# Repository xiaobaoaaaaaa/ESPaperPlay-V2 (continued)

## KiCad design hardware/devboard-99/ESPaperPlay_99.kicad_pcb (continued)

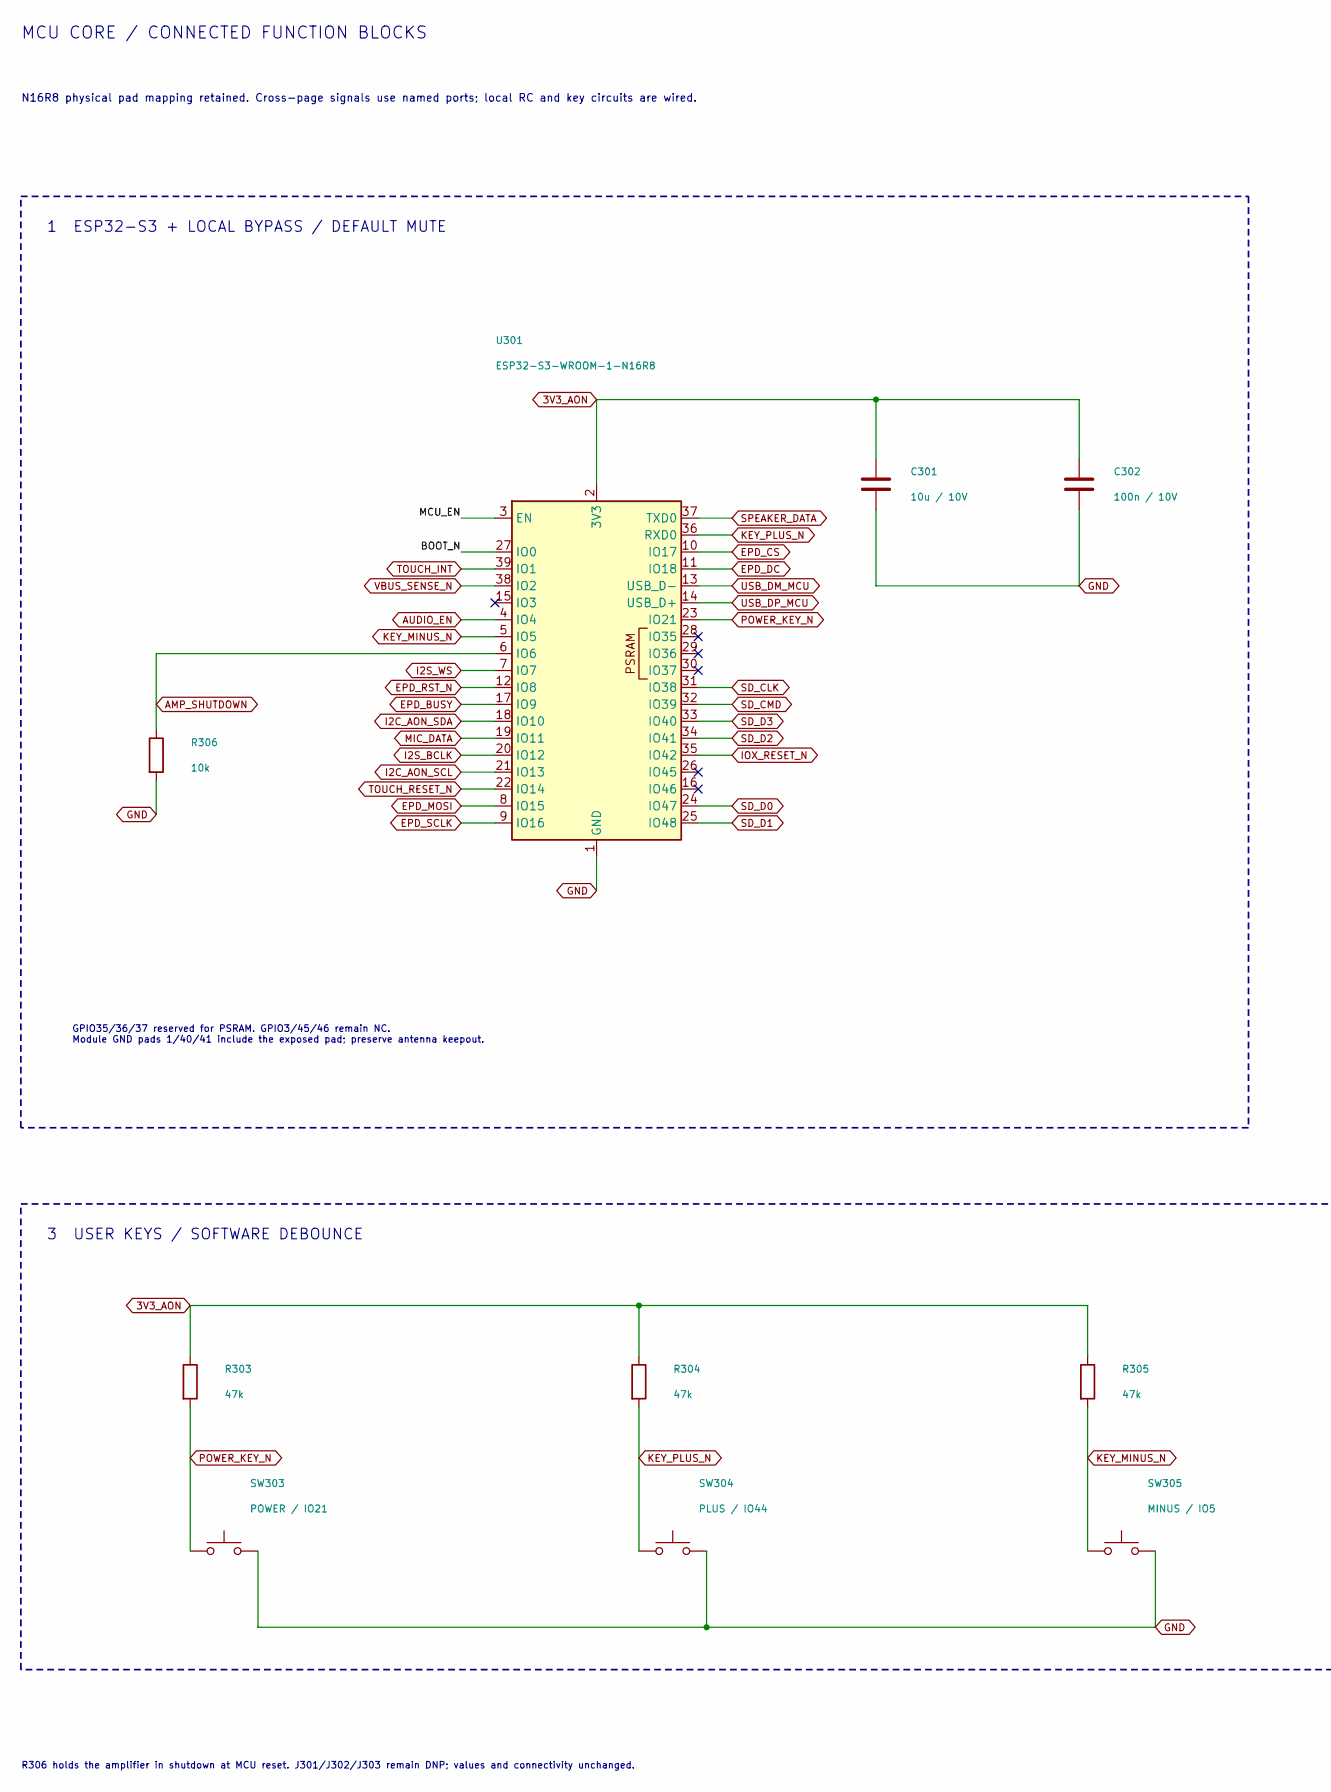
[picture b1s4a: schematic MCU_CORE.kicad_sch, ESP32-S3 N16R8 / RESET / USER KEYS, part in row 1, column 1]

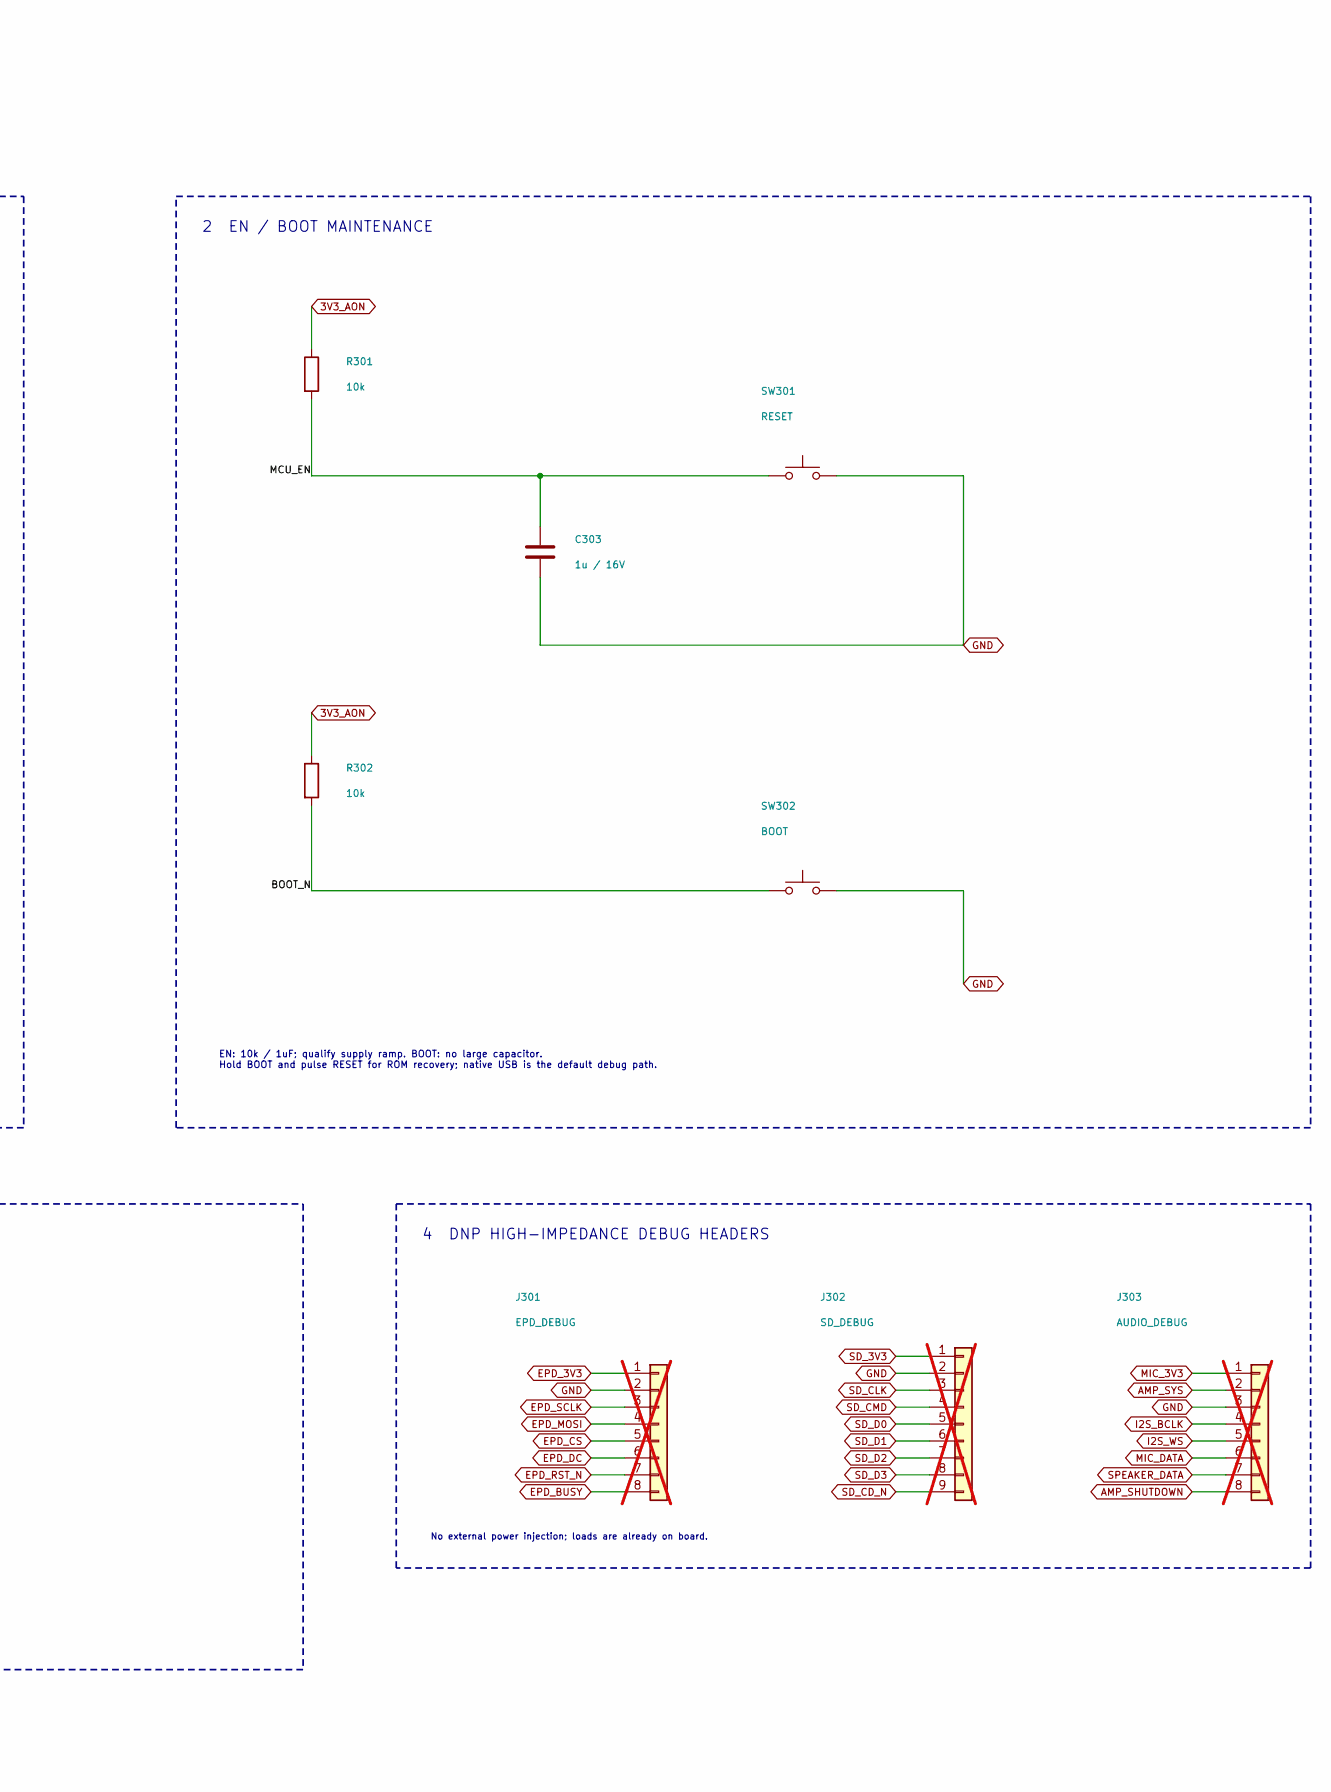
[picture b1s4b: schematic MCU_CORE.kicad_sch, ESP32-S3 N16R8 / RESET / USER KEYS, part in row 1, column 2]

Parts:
C301: 10u / 10V; C_0805_2012Metric
C302: 100n / 10V; C_0603_1608Metric
C303: 1u / 16V; C_0603_1608Metric
J301: EPD_DEBUG; WR_PHD_1x08_P2.54_Drill1.10; not fitted
J302: SD_DEBUG; WR_PHD_1x09_P2.54_Drill1.10; not fitted
J303: AUDIO_DEBUG; WR_PHD_1x08_P2.54_Drill1.10; not fitted
R301, R302, R306: 10k; R_0603_1608Metric
R303, R304, R305: 47k; R_0603_1608Metric
SW301: RESET; SW_PUSH_6mm
SW302: BOOT; SW_PUSH_6mm
SW303: POWER / IO21; SW_PUSH_6mm
SW304: PLUS / IO44; SW_PUSH_6mm
SW305: MINUS / IO5; SW_PUSH_6mm
U301: ESP32-S3-WROOM-1-N16R8; ESP32-S3-WROOM-1_030mm_PTH

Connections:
3V3_AON: C301.1, C302.1, R301.1, R302.1, R303.1, R304.1, R305.1, U301.2 (3V3); also elsewhere on the board
/MCU_CORE/BOOT_N: R302.2, SW302.1, U301.27 (IO0)
/MCU_CORE/MCU_EN: C303.1, R301.2, SW301.1, U301.3 (EN)
AMP_SHUTDOWN: J303.8, R306.1, U301.6 (IO6); also elsewhere on the board
AMP_SYS: J303.2; also elsewhere on the board
AUDIO_EN: U301.4 (IO4); also elsewhere on the board
EPD_3V3: J301.1; also elsewhere on the board
EPD_BUSY: J301.8, U301.17 (IO9); also elsewhere on the board
EPD_CS: J301.5, U301.10 (IO17); also elsewhere on the board
EPD_DC: J301.6, U301.11 (IO18); also elsewhere on the board
EPD_MOSI: J301.4, U301.8 (IO15); also elsewhere on the board
EPD_RST_N: J301.7, U301.12 (IO8); also elsewhere on the board
EPD_SCLK: J301.3, U301.9 (IO16); also elsewhere on the board
GND: C301.2, C302.2, C303.2, J301.2, J302.2, J303.3, R306.2, SW301.2, SW302.2, SW303.2, SW304.2, SW305.2, U301.1 (GND), U301.40 (GND), U301.41 (GND); also elsewhere on the board
I2C_AON_SCL: U301.21 (IO13); also elsewhere on the board
I2C_AON_SDA: U301.18 (IO10); also elsewhere on the board
I2S_BCLK: J303.4, U301.20 (IO12); also elsewhere on the board
I2S_WS: J303.5, U301.7 (IO7); also elsewhere on the board
IOX_RESET_N: U301.35 (IO42); also elsewhere on the board
KEY_MINUS_N: R305.2, SW305.1, U301.5 (IO5)
KEY_PLUS_N: R304.2, SW304.1, U301.36 (RXD0)
MIC_3V3: J303.1; also elsewhere on the board
MIC_DATA: J303.6, U301.19 (IO11); also elsewhere on the board
POWER_KEY_N: R303.2, SW303.1, U301.23 (IO21)
SD_3V3: J302.1; also elsewhere on the board
SD_CD_N: J302.9; also elsewhere on the board
SD_CLK: J302.3, U301.31 (IO38); also elsewhere on the board
SD_CMD: J302.4, U301.32 (IO39); also elsewhere on the board
SD_D0: J302.5, U301.24 (IO47); also elsewhere on the board
SD_D1: J302.6, U301.25 (IO48); also elsewhere on the board
SD_D2: J302.7, U301.34 (IO41); also elsewhere on the board
SD_D3: J302.8, U301.33 (IO40); also elsewhere on the board
SPEAKER_DATA: J303.7, U301.37 (TXD0); also elsewhere on the board
TOUCH_INT: U301.39 (IO1); also elsewhere on the board
TOUCH_RESET_N: U301.22 (IO14); also elsewhere on the board
USB_DM_MCU: U301.13 (USB_D-); also elsewhere on the board
USB_DP_MCU: U301.14 (USB_D+); also elsewhere on the board
VBUS_SENSE_N: U301.38 (IO2); also elsewhere on the board

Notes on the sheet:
MCU CORE / CONNECTED FUNCTION BLOCKS
N16R8 physical pad mapping retained. Cross-page signals use named ports; local RC and key circuits are wired.
1 ESP32-S3 + LOCAL BYPASS / DEFAULT MUTE
GPIO35/36/37 reserved for PSRAM. GPIO3/45/46 remain NC. Module GND pads 1/40/41 include the exposed pad; preserve antenna keepout.
2 EN / BOOT MAINTENANCE
EN: 10k / 1uF; qualify supply ramp. BOOT: no large capacitor. Hold BOOT and pulse RESET for ROM recovery; native USB is the default debug path.
3 USER KEYS / SOFTWARE DEBOUNCE
4 DNP HIGH-IMPEDANCE DEBUG HEADERS
No external power injection; loads are already on board.
R306 holds the amplifier in shutdown at MCU reset. J301/J302/J303 remain DNP; values and connectivity unchanged.

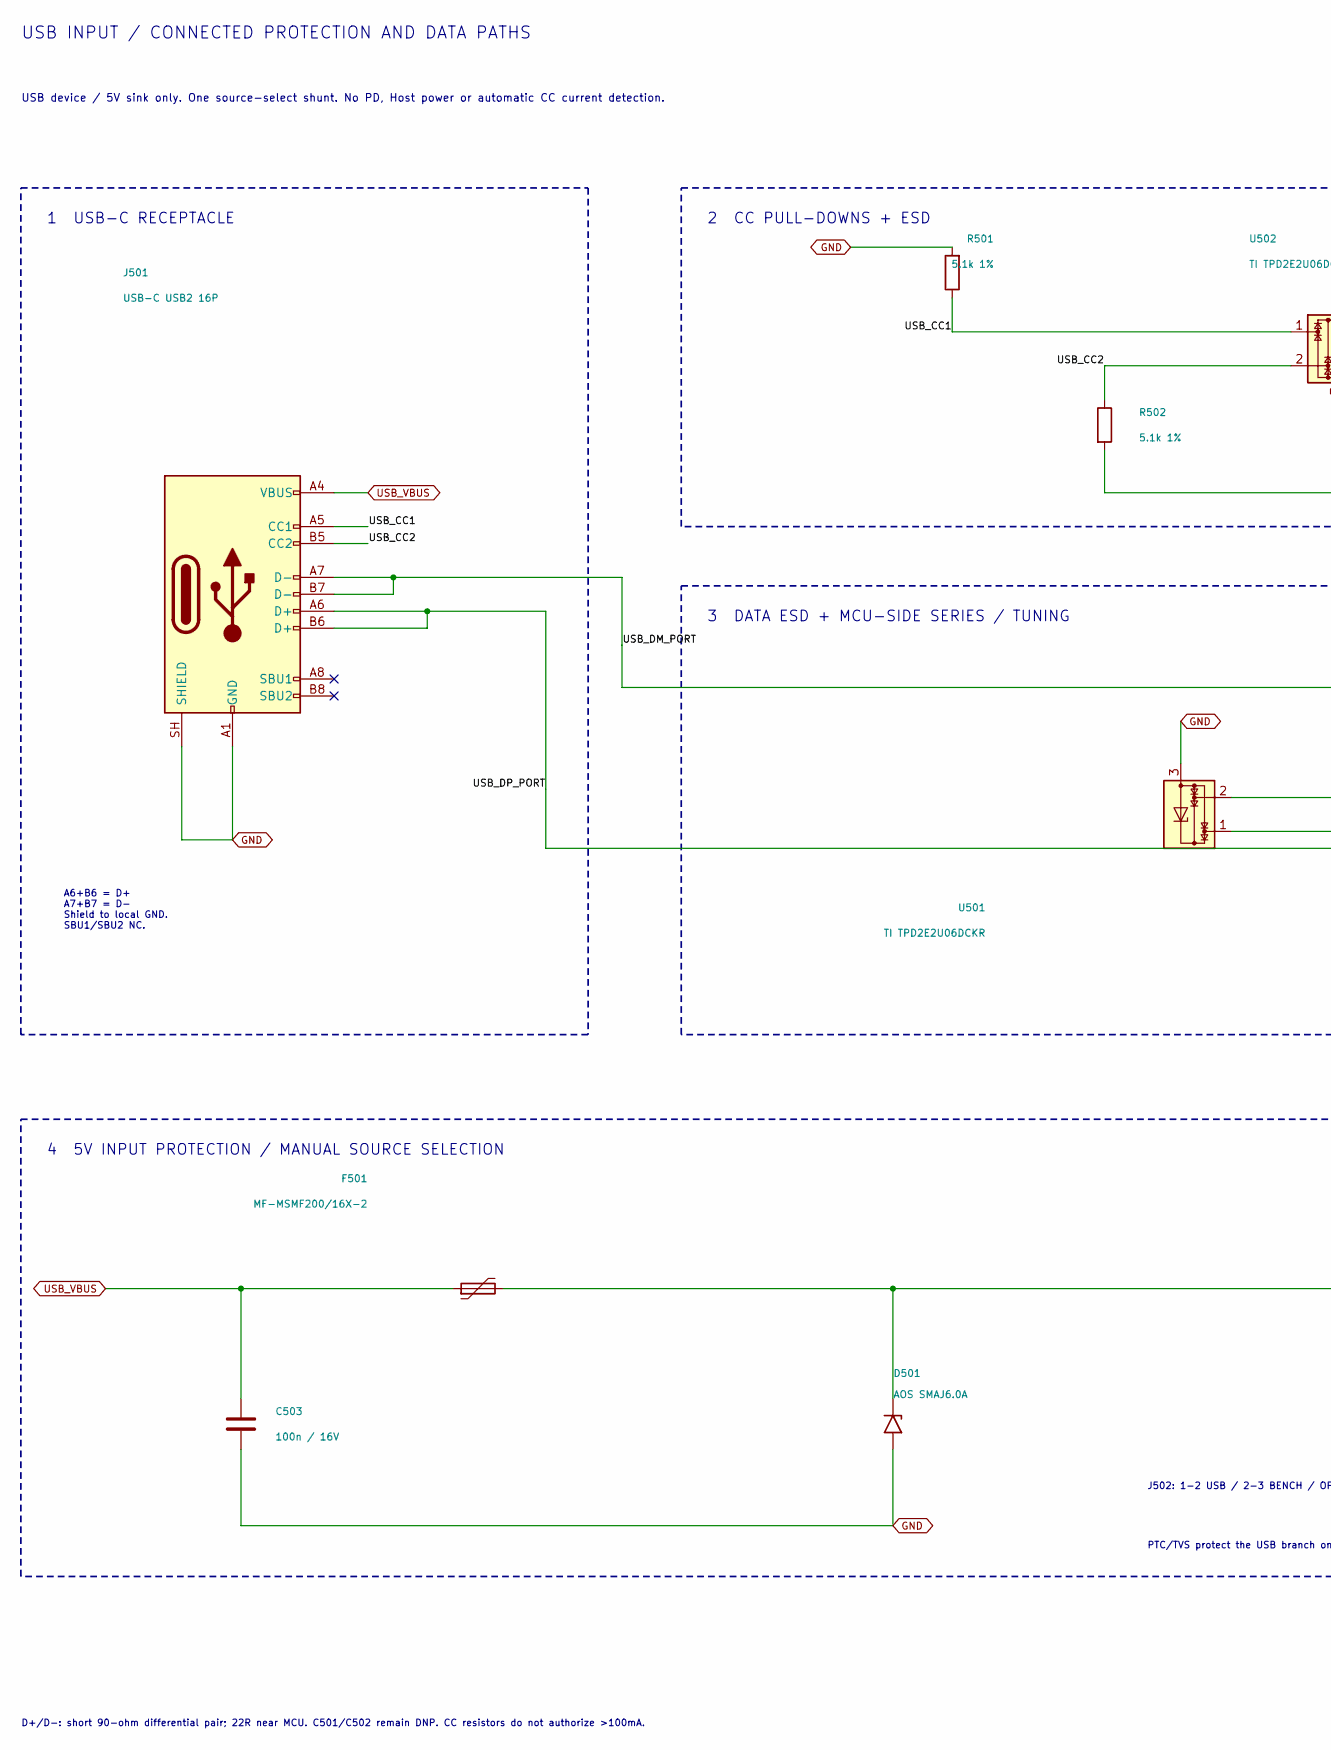
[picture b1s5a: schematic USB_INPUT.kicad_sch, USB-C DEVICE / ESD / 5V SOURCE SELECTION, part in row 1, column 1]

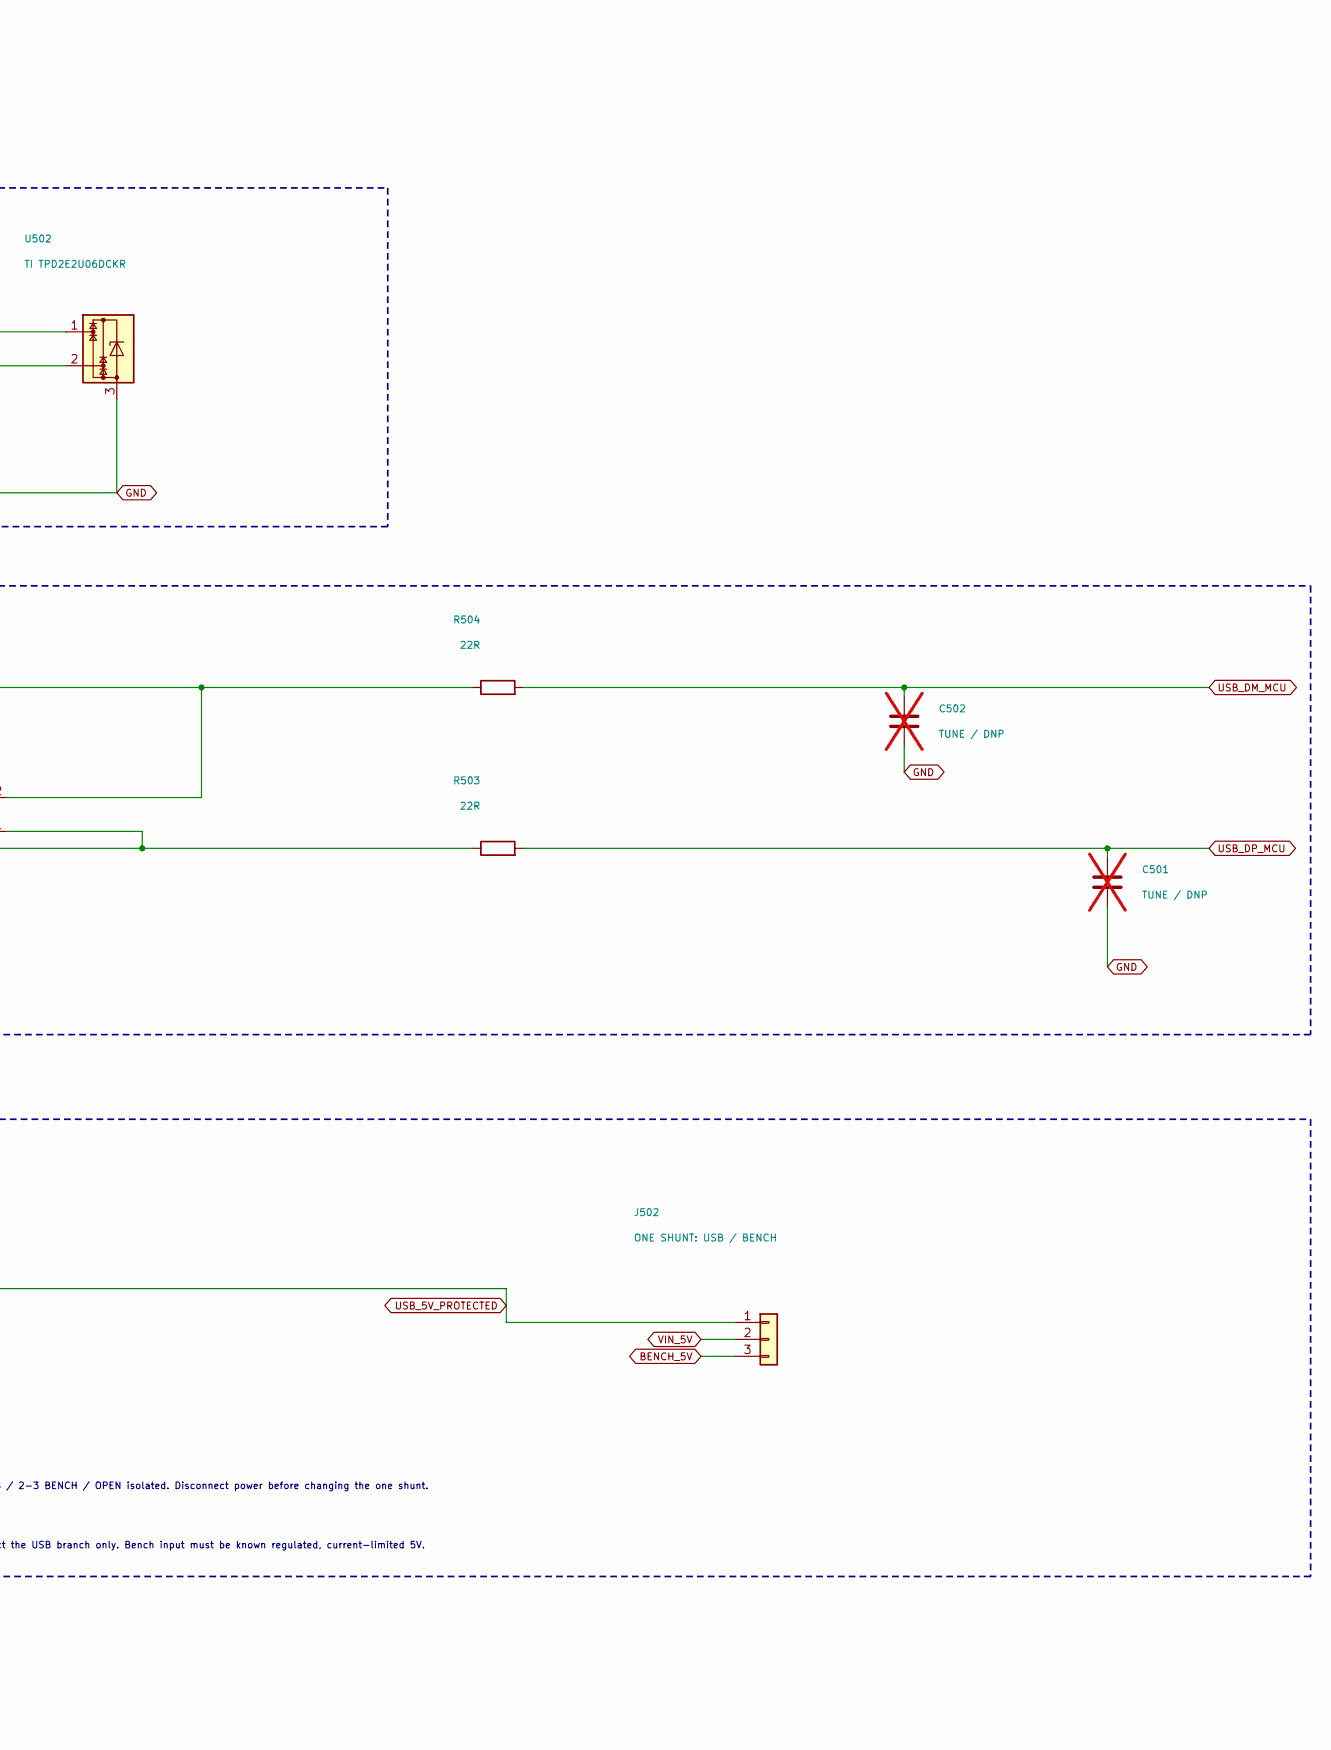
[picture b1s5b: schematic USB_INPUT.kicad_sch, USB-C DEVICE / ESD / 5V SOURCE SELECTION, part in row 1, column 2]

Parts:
C501, C502: TUNE / DNP; C_0603_1608Metric; not fitted
C503: 100n / 16V; C_0603_1608Metric
D501: AOS SMAJ6.0A; D_SMA
F501: MF-MSMF200/16X-2; Bourns_MF-MSMF_1812_Style2
J501: USB-C USB2 16P; USB_C_Receptacle_GCT_USB4105-xx-A_16P_TopMnt_Horizontal
J502: ONE SHUNT: USB / BENCH; WR_PHD_1x03_P2.54_Drill1.10
R501, R502: 5.1k 1%; R_0603_1608Metric
R503, R504: 22R; R_0603_1608Metric
U501, U502: TI TPD2E2U06DCKR; TI_DCK0003A_SC70_3_Recommended

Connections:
/USB_INPUT/USB_CC1: J501.A5 (CC1), R501.1, U502.1
/USB_INPUT/USB_CC2: J501.B5 (CC2), R502.1, U502.2
/USB_INPUT/USB_DM_PORT: J501.A7 (D-), J501.B7 (D-), R504.1, U501.2
/USB_INPUT/USB_DP_PORT: J501.A6 (D+), J501.B6 (D+), R503.1, U501.1
BENCH_5V: J502.3; also elsewhere on the board
GND: C501.2, C502.2, C503.2, D501.2 (A2), J501.A1 (GND), J501.A12 (GND), J501.B1 (GND), J501.B12 (GND), J501.SH (SHIELD), R501.2, R502.2, U501.3, U502.3; also elsewhere on the board
USB_5V_PROTECTED: D501.1 (A1), F501.2, J502.1; also elsewhere on the board
USB_DM_MCU: C502.1, R504.2; also elsewhere on the board
USB_DP_MCU: C501.1, R503.2; also elsewhere on the board
USB_VBUS: C503.1, F501.1, J501.A4 (VBUS), J501.A9 (VBUS), J501.B4 (VBUS), J501.B9 (VBUS)
VIN_5V: J502.2; also elsewhere on the board

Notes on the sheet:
USB INPUT / CONNECTED PROTECTION AND DATA PATHS
USB device / 5V sink only. One source-select shunt. No PD, Host power or automatic CC current detection.
1 USB-C RECEPTACLE
A6+B6 = D+ A7+B7 = D- Shield to local GND. SBU1/SBU2 NC.
2 CC PULL-DOWNS + ESD
3 DATA ESD + MCU-SIDE SERIES / TUNING
4 5V INPUT PROTECTION / MANUAL SOURCE SELECTION
J502: 1-2 USB / 2-3 BENCH / OPEN isolated. Disconnect power before changing the one shunt.
PTC/TVS protect the USB branch only. Bench input must be known regulated, current-limited 5V.
D+/D-: short 90-ohm differential pair; 22R near MCU. C501/C502 remain DNP. CC resistors do not authorize >100mA.

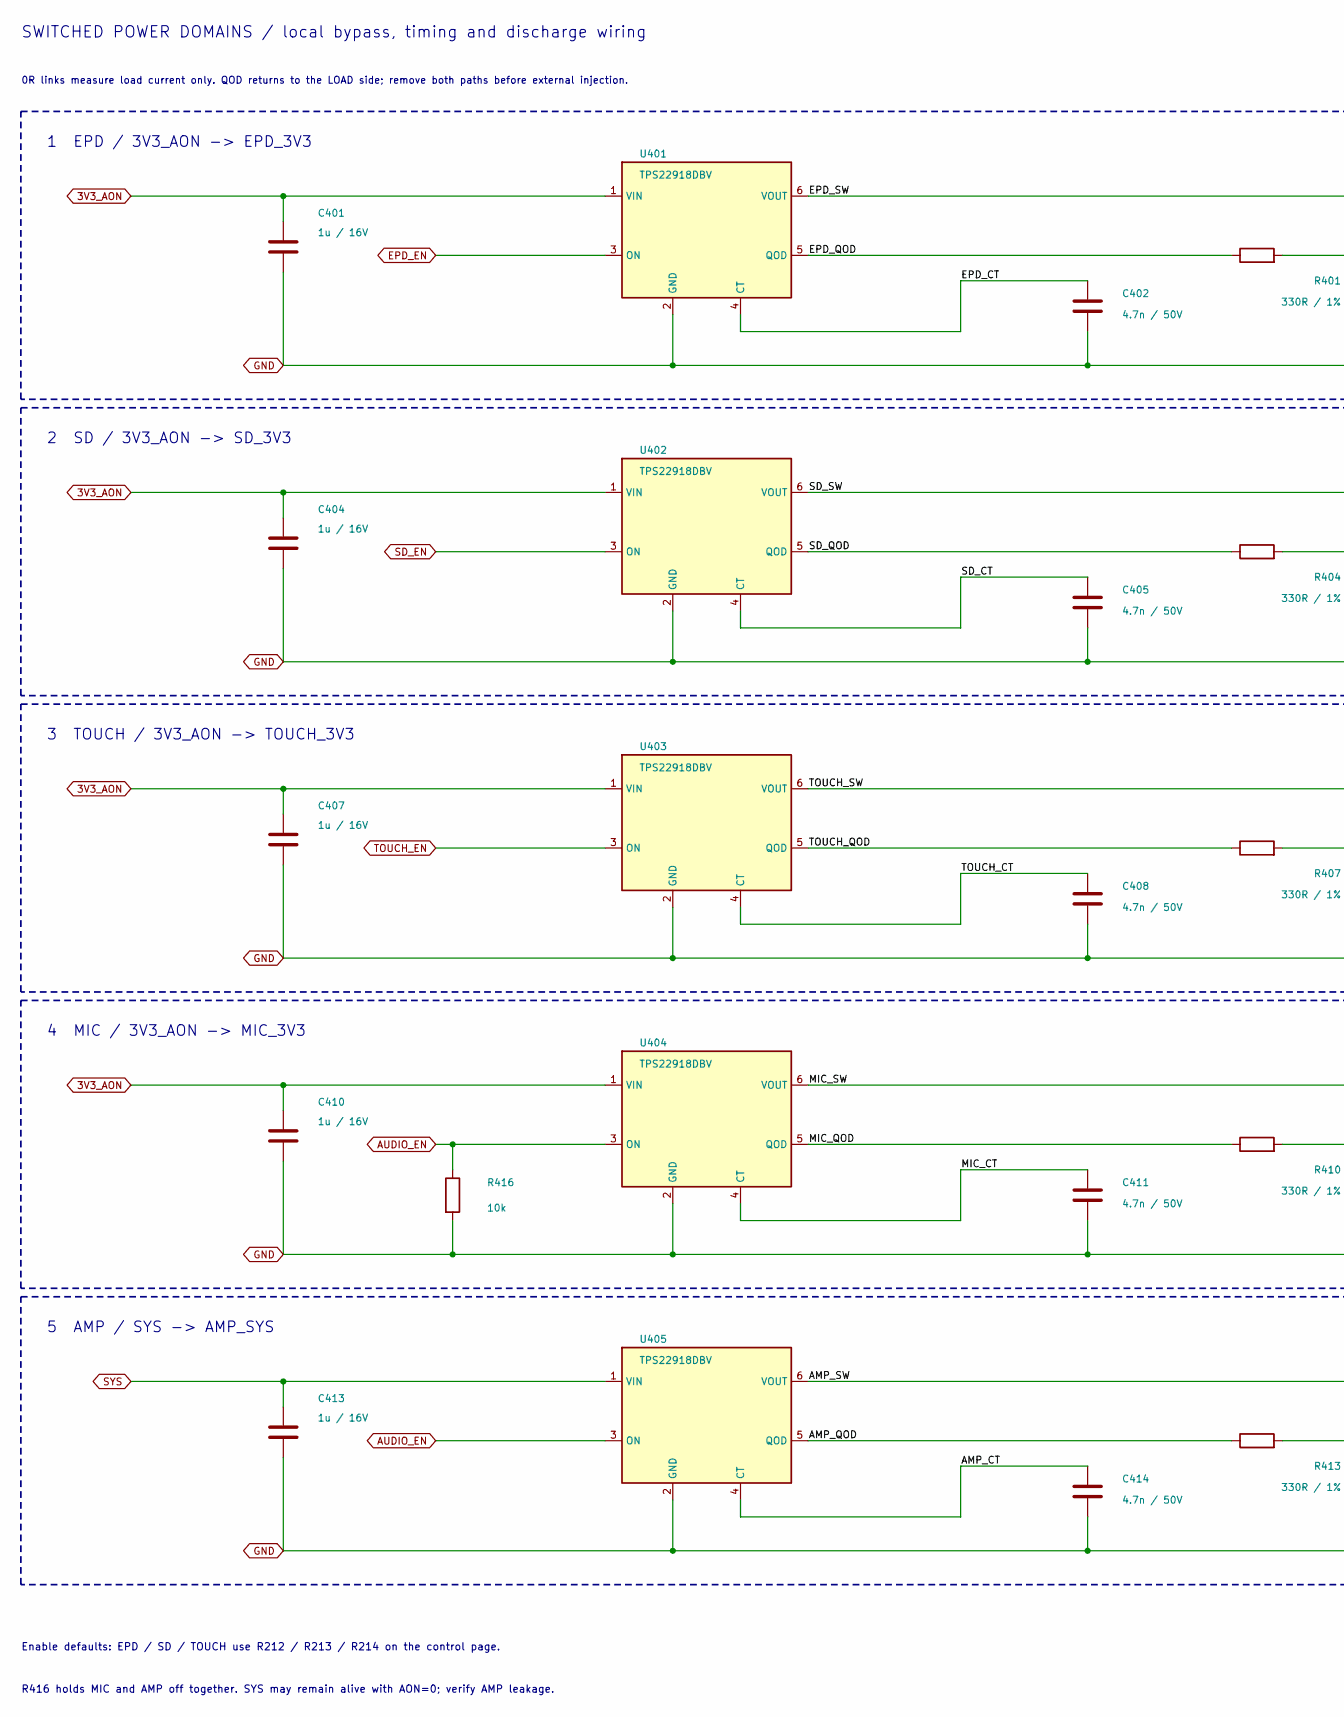
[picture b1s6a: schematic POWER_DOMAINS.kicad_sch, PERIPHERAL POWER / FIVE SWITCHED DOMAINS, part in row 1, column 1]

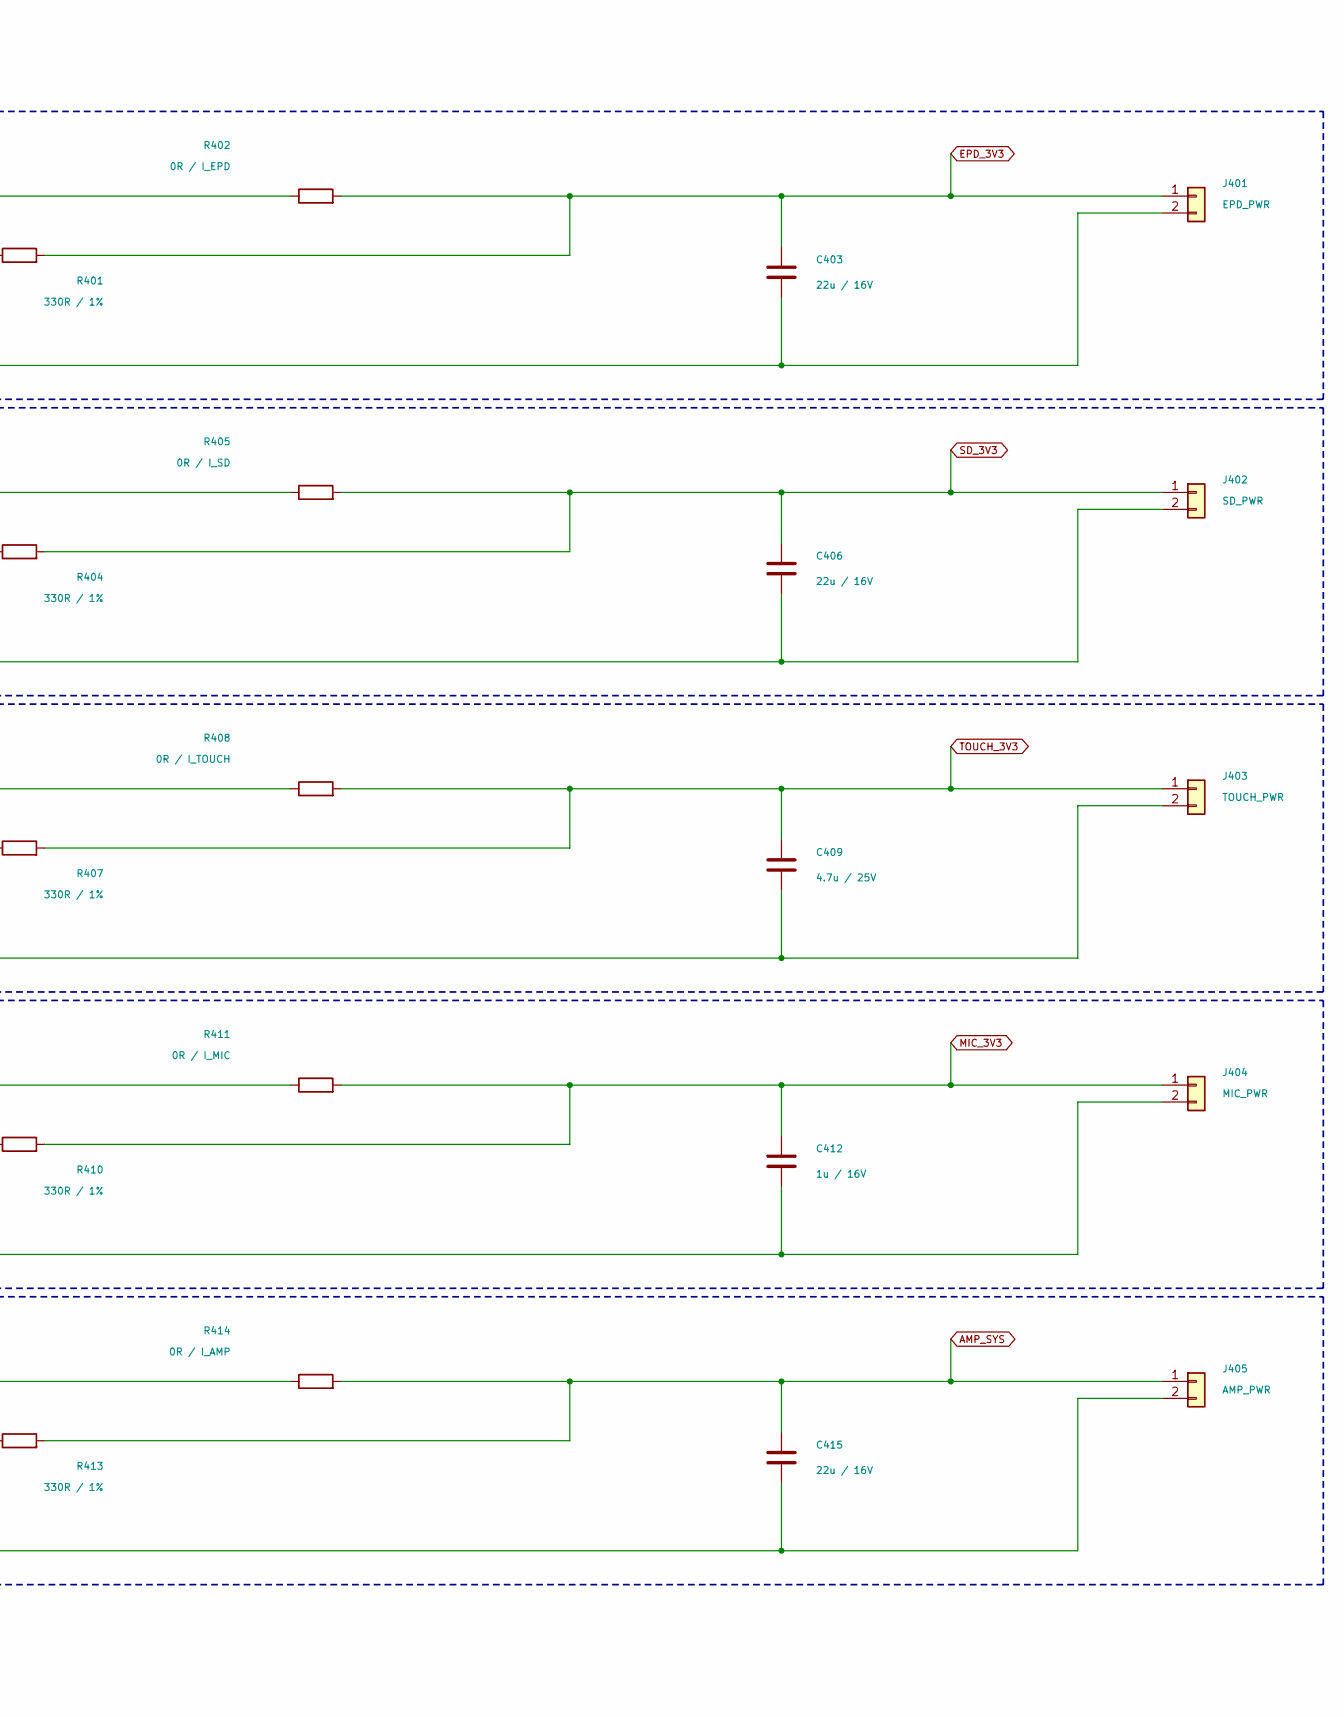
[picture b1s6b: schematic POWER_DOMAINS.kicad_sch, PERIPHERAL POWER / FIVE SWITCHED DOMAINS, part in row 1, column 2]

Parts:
C401, C404, C407, C410, C412, C413: 1u / 16V; C_0603_1608Metric
C402, C405, C408, C411, C414: 4.7n / 50V; C_0603_1608Metric
C403, C406, C415: 22u / 16V; C_1206_3216Metric
C409: 4.7u / 25V; C_0805_2012Metric
J401: EPD_PWR; WR_PHD_1x02_P2.54_Drill1.10
J402: SD_PWR; WR_PHD_1x02_P2.54_Drill1.10
J403: TOUCH_PWR; WR_PHD_1x02_P2.54_Drill1.10
J404: MIC_PWR; WR_PHD_1x02_P2.54_Drill1.10
J405: AMP_PWR; WR_PHD_1x02_P2.54_Drill1.10
R401, R404, R407, R410, R413: 330R / 1%; R_0603_1608Metric
R402: 0R / I_EPD; Bourns_CRF0805_Jumper
R405: 0R / I_SD; Bourns_CRF0805_Jumper
R408: 0R / I_TOUCH; Bourns_CRF0805_Jumper
R411: 0R / I_MIC; Bourns_CRF0805_Jumper
R414: 0R / I_AMP; Bourns_CRF0805_Jumper
R416: 10k; R_0603_1608Metric
U401, U402, U403, U404, U405: TPS22918DBV; SOT-23-6

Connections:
3V3_AON: C401.1, C404.1, C407.1, C410.1, U401.1 (VIN), U402.1 (VIN), U403.1 (VIN), U404.1 (VIN); also elsewhere on the board
/POWER_DOMAINS/AMP_CT: C414.1, U405.4 (CT)
/POWER_DOMAINS/AMP_QOD: R413.1, U405.5 (QOD)
/POWER_DOMAINS/AMP_SW: R414.1, U405.6 (VOUT)
/POWER_DOMAINS/EPD_CT: C402.1, U401.4 (CT)
/POWER_DOMAINS/EPD_QOD: R401.1, U401.5 (QOD)
/POWER_DOMAINS/EPD_SW: R402.1, U401.6 (VOUT)
/POWER_DOMAINS/MIC_CT: C411.1, U404.4 (CT)
/POWER_DOMAINS/MIC_QOD: R410.1, U404.5 (QOD)
/POWER_DOMAINS/MIC_SW: R411.1, U404.6 (VOUT)
/POWER_DOMAINS/SD_CT: C405.1, U402.4 (CT)
/POWER_DOMAINS/SD_QOD: R404.1, U402.5 (QOD)
/POWER_DOMAINS/SD_SW: R405.1, U402.6 (VOUT)
/POWER_DOMAINS/TOUCH_CT: C408.1, U403.4 (CT)
/POWER_DOMAINS/TOUCH_QOD: R407.1, U403.5 (QOD)
/POWER_DOMAINS/TOUCH_SW: R408.1, U403.6 (VOUT)
AMP_SYS: C415.1, J405.1, R413.2, R414.2; also elsewhere on the board
AUDIO_EN: R416.1, U404.3 (ON), U405.3 (ON); also elsewhere on the board
EPD_3V3: C403.1, J401.1, R401.2, R402.2; also elsewhere on the board
EPD_EN: U401.3 (ON); also elsewhere on the board
GND: C401.2, C402.2, C403.2, C404.2, C405.2, C406.2, C407.2, C408.2, C409.2, C410.2, C411.2, C412.2, C413.2, C414.2, C415.2, J401.2, J402.2, J403.2, J404.2, J405.2, R416.2, U401.2 (GND), U402.2 (GND), U403.2 (GND), U404.2 (GND), U405.2 (GND); also elsewhere on the board
MIC_3V3: C412.1, J404.1, R410.2, R411.2; also elsewhere on the board
SD_3V3: C406.1, J402.1, R404.2, R405.2; also elsewhere on the board
SD_EN: U402.3 (ON); also elsewhere on the board
SYS: C413.1, U405.1 (VIN); also elsewhere on the board
TOUCH_3V3: C409.1, J403.1, R407.2, R408.2; also elsewhere on the board
TOUCH_EN: U403.3 (ON); also elsewhere on the board

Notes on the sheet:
SWITCHED POWER DOMAINS / local bypass, timing and discharge wiring
0R links measure load current only. QOD returns to the LOAD side; remove both paths before external injection.
1 EPD / 3V3_AON -> EPD_3V3
2 SD / 3V3_AON -> SD_3V3
3 TOUCH / 3V3_AON -> TOUCH_3V3
4 MIC / 3V3_AON -> MIC_3V3
5 AMP / SYS -> AMP_SYS
Enable defaults: EPD / SD / TOUCH use R212 / R213 / R214 on the control page.
R416 holds MIC and AMP off together. SYS may remain alive with AON=0; verify AMP leakage.
